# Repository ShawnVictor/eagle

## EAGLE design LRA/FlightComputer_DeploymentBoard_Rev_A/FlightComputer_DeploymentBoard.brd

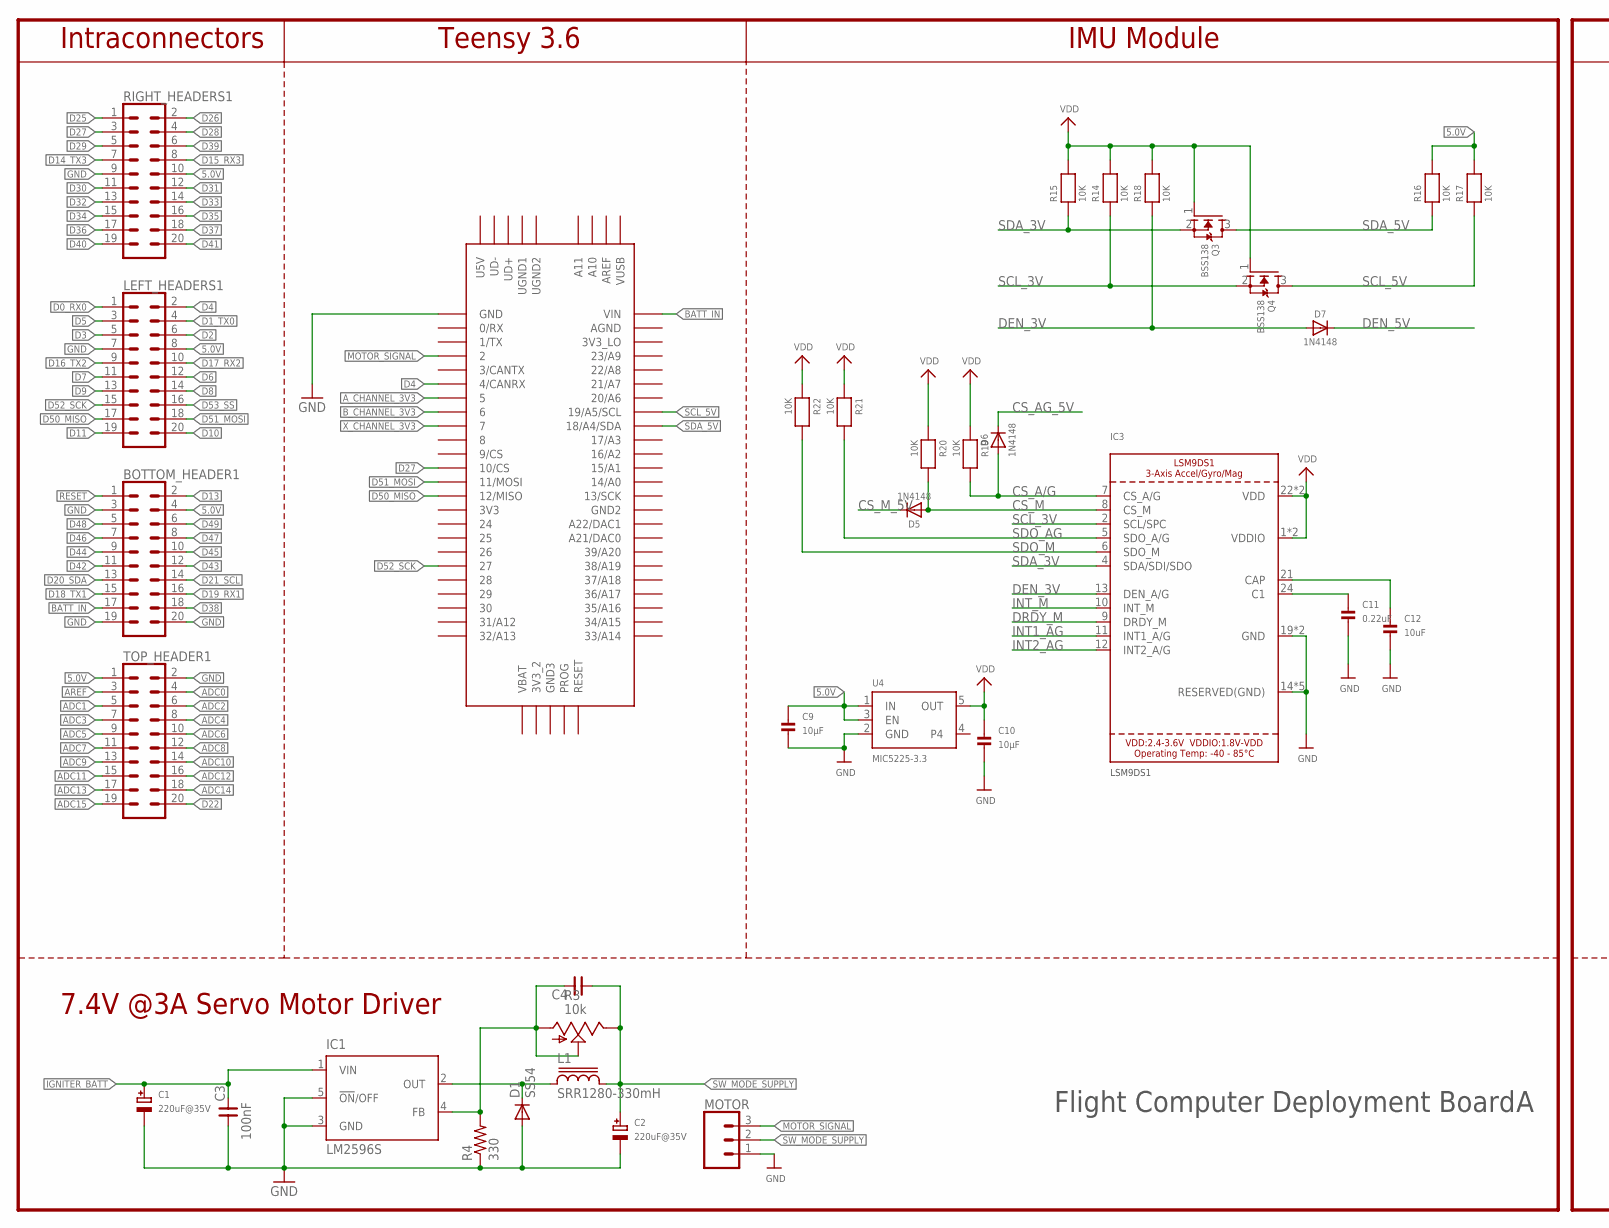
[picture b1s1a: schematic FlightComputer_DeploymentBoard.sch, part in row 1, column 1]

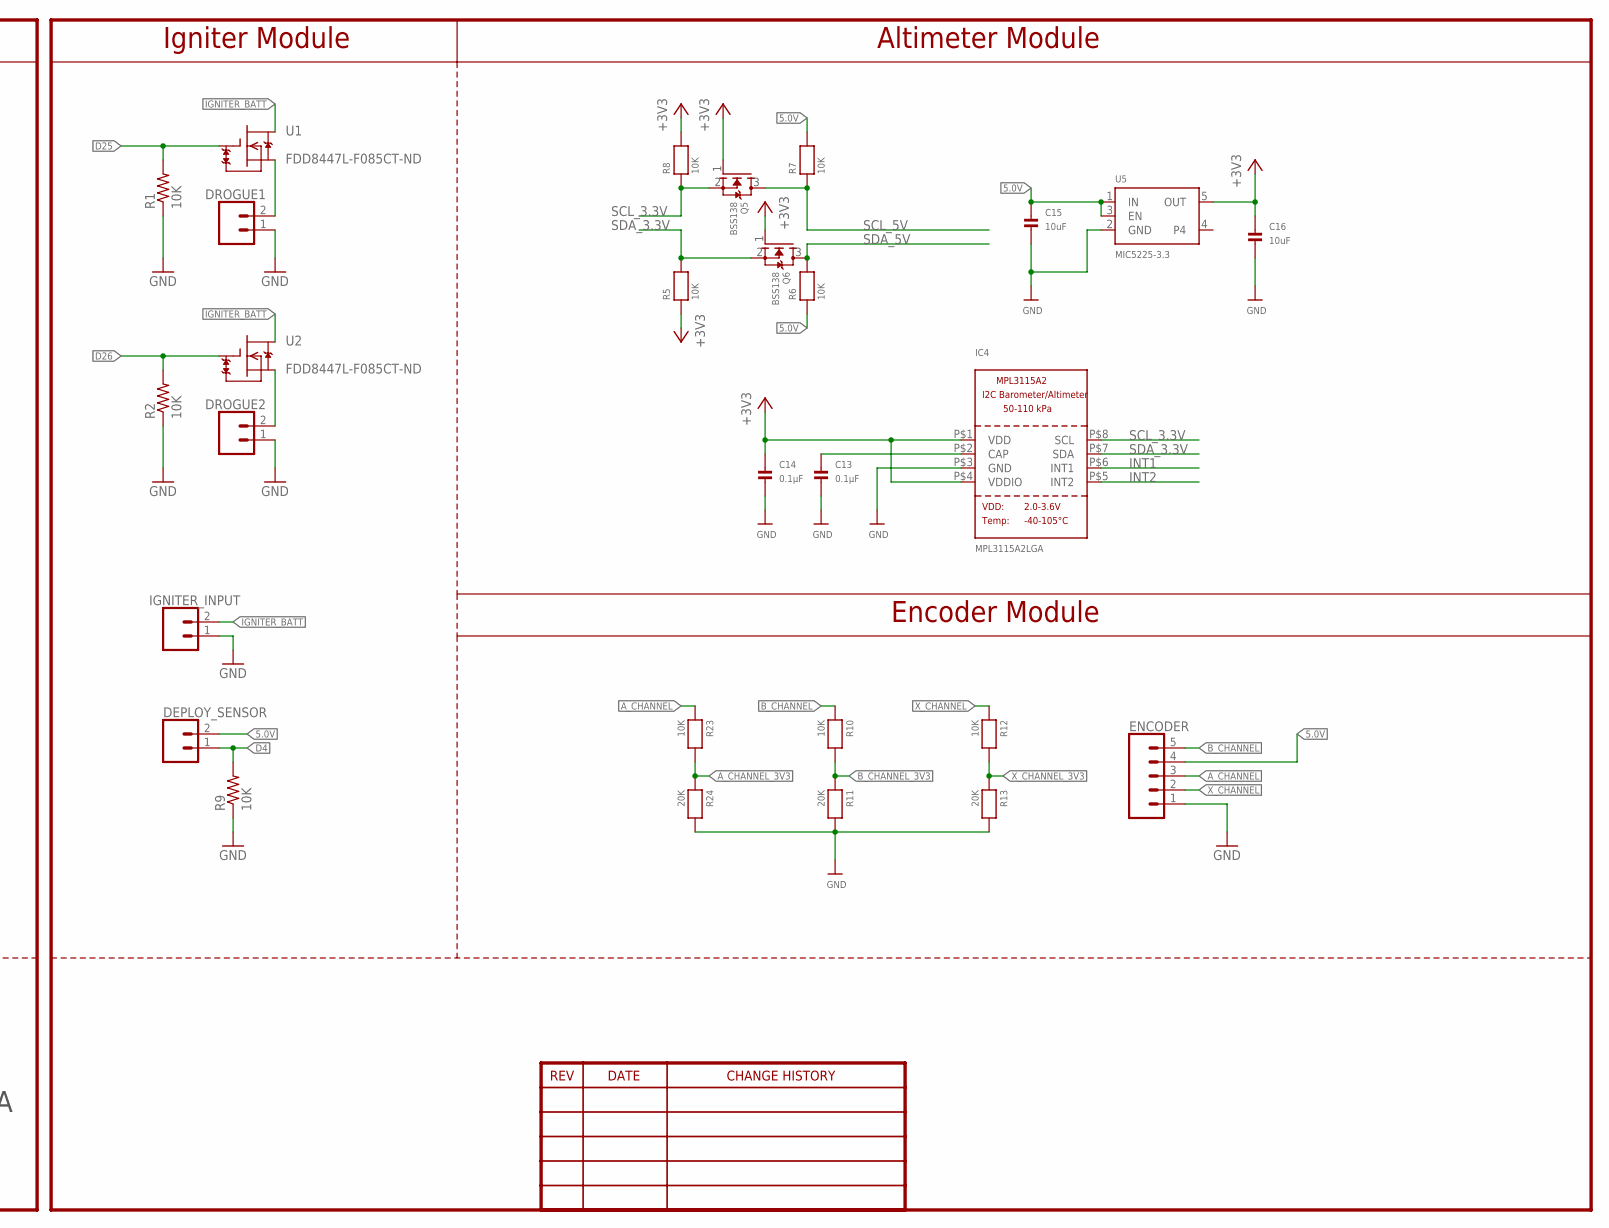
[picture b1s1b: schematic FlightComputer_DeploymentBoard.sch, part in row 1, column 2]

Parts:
BOTTOM_HEADER1: CONN_10X2; 2X10
C1, C2: 220uF@35V; PANASONIC_D
C3: 100nF; 0603
C4: CNP-0603; 0603
C9, C10: 10µF; 0603
C11: 0.22uF; 0603
C12, C15, C16: 10uF; 0603
C13, C14: 0.1µF; 0603
D1: SS54; DO214AB
D5, D6, D7: 1N4148; SOD-323
DEPLOY_SENSOR: CONN_023.5MM; SCREWTERMINAL-3.5MM-2
DROGUE1, DROGUE2: CONN_023.5MM; SCREWTERMINAL-3.5MM-2
ENCODER: CONN_05; 1X05
IC1: LM2596S; TO263-5
IC3: LSM9DS1; LGA24_3.5X3.1MM
IC4: MPL3115A2LGA; LGA8
IGNITER_INPUT: CONN_02; 1X02
L1: SRR1280-330mH; SRR1280
LEFT_HEADERS1: CONN_10X2; 2X10
MOTOR: CONN_03; 1X03
Q3, Q4, Q5, Q6: BSS138; SOT23-WIDE
R1, R2, R9: 10K; R0805
R3: 10k; S64W
R4: 330; R0603
R5, R6, R7, R8, R10, R12, R14, R15, R16, R17, R18, R19, R20, R21, R22, R23: 10K; 0603
R11, R13, R24: 20K; 0603
RIGHT_HEADERS1: CONN_10X2; 2X10
TOP_HEADER1: CONN_10X2; 2X10
U1, U2: FDD8447L-F085CT-ND; TO252
U4, U5: MIC5225-3.3; SOT23-5
U$1: TEENSY_3.5/3.6

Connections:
5.0V: BOTTOM_HEADER1.4, C9.1, C15.1, DEPLOY_SENSOR.2, ENCODER.4, LEFT_HEADERS1.8, R6.1, R7.2, R16.2, R17.2, RIGHT_HEADERS1.10, TOP_HEADER1.1, U4.1 (IN), U4.3 (EN), U5.1 (IN), U5.3 (EN)
+3V3: C14.1, C16.1, IC4.P$1 (VDD), IC4.P$4 (VDDIO), Q5.1 (G), Q6.1 (G), R5.1, R8.2, U5.5 (OUT)
ADC0: TOP_HEADER1.4
ADC1: TOP_HEADER1.5
ADC2: TOP_HEADER1.6
ADC3: TOP_HEADER1.7
ADC4: TOP_HEADER1.8
ADC5: TOP_HEADER1.9
ADC6: TOP_HEADER1.10
ADC7: TOP_HEADER1.11
ADC8: TOP_HEADER1.12
ADC9: TOP_HEADER1.13
ADC10: TOP_HEADER1.14
ADC11: TOP_HEADER1.15
ADC12: TOP_HEADER1.16
ADC13: TOP_HEADER1.17
ADC14: TOP_HEADER1.18
ADC15: TOP_HEADER1.19
AREF: TOP_HEADER1.3
A_CHANNEL: ENCODER.3, R23.1
A_CHANNEL_3V3: R23.2, R24.1, U$1.5
BATT_IN: BOTTOM_HEADER1.17, U$1.VIN
B_CHANNEL: ENCODER.5, R10.1
B_CHANNEL_3V3: R10.2, R11.1, U$1.6
C2: C11.1, IC3.24 (C1)
CAP1: C12.1, IC3.21 (CAP)
CAP2: C13.1, IC4.P$2 (CAP)
CS_A/G: D6.A, IC3.7 (CS_A/G), R19.2
CS_AG_5V: D6.C
CS_M: D5.A, IC3.8 (CS_M), R20.2
CS_M_5V: D5.C
D0_RX0: LEFT_HEADERS1.1
D1_TX0: LEFT_HEADERS1.4
D2: LEFT_HEADERS1.6
D3: LEFT_HEADERS1.5
D4: DEPLOY_SENSOR.1, LEFT_HEADERS1.2, R9.2, U$1.4/CANRX
D5: LEFT_HEADERS1.3
D6: LEFT_HEADERS1.12
D7: LEFT_HEADERS1.11
D8: LEFT_HEADERS1.14
D9: LEFT_HEADERS1.13
D10: LEFT_HEADERS1.20
D11: LEFT_HEADERS1.19
D13: BOTTOM_HEADER1.2
D14_TX3: RIGHT_HEADERS1.7
D15_RX3: RIGHT_HEADERS1.8
D16_TX2: LEFT_HEADERS1.9
D17_RX2: LEFT_HEADERS1.10
D18_TX1: BOTTOM_HEADER1.15
D19_RX1: BOTTOM_HEADER1.16
D20_SDA: BOTTOM_HEADER1.13
D21_SCL: BOTTOM_HEADER1.14
D22: TOP_HEADER1.20
D25: R1.2, RIGHT_HEADERS1.1, U1.G
D26: R2.2, RIGHT_HEADERS1.2, U2.G
D27: RIGHT_HEADERS1.3, U$1.10/CS
D28: RIGHT_HEADERS1.4
D29: RIGHT_HEADERS1.5
D30: RIGHT_HEADERS1.11
D31: RIGHT_HEADERS1.12
D32: RIGHT_HEADERS1.13
D33: RIGHT_HEADERS1.14
D34: RIGHT_HEADERS1.15
D35: RIGHT_HEADERS1.16
D36: RIGHT_HEADERS1.17
D37: RIGHT_HEADERS1.18
D38: BOTTOM_HEADER1.18
D39: RIGHT_HEADERS1.6
D40: RIGHT_HEADERS1.19
D41: RIGHT_HEADERS1.20
D42: BOTTOM_HEADER1.11
D43: BOTTOM_HEADER1.12
D44: BOTTOM_HEADER1.9
D45: BOTTOM_HEADER1.10
D46: BOTTOM_HEADER1.7
D47: BOTTOM_HEADER1.8
D48: BOTTOM_HEADER1.5
D49: BOTTOM_HEADER1.6
D50_MISO: LEFT_HEADERS1.17, U$1.12/MISO
D51_MOSI: LEFT_HEADERS1.18, U$1.11/MOSI
D52_SCK: LEFT_HEADERS1.15, U$1.27
D53_SS: LEFT_HEADERS1.16
DEN_3V: D7.A, IC3.13 (DEN_A/G), R18.1
DEN_5V: D7.C
DRDY_M: IC3.9 (DRDY_M)
GND: BOTTOM_HEADER1.3, BOTTOM_HEADER1.19, BOTTOM_HEADER1.20, C1.-, C2.-, C3.1, C9.2, C10.2, C11.2, C12.2, C13.2, C14.2, C15.2, C16.2, D1.A, DROGUE1.1, DROGUE2.1, ENCODER.1, IC1.3 (GND), IC1.5 (!ON!/OFF), IC3.14 (RESERVED(GND)), IC3.15 (RESERVED(GND)), IC3.16 (RESERVED(GND)), IC3.17 (RESERVED(GND)), IC3.18 (RESERVED(GND)), IC3.19 (GND), IC3.20 (GND), IC4.P$3 (GND), IGNITER_INPUT.1, LEFT_HEADERS1.7, MOTOR.1, R1.1, R2.1, R4.1, R9.1, R11.2, R13.2, R24.2, RIGHT_HEADERS1.9, TOP_HEADER1.2, U4.2 (GND), U5.2 (GND), U$1.GND
IGNITER_BATT: C1.+, C3.2, IC1.1 (VIN), IGNITER_INPUT.2, U1.D, U2.D
INT1: IC4.P$6 (INT1)
INT1_AG: IC3.11 (INT1_A/G)
INT2: IC4.P$5 (INT2)
INT2_AG: IC3.12 (INT2_A/G)
INT_M: IC3.10 (INT_M)
MOTOR_SIGNAL: MOTOR.3, U$1.2
unnamed: D1.C, IC1.2 (OUT), L1.1
unnamed: C4.2, IC1.4 (FB), R3.A, R3.S, R4.2
RESET: BOTTOM_HEADER1.1
SCL_3.3V: IC4.P$8 (SCL), Q5.2 (S), R8.1
SCL_3V: IC3.2 (SCL/SPC), Q4.2 (S), R14.1
SCL_5V: Q4.3 (D), Q5.3 (D), R7.1, R17.1, U$1.19/A5/SCL
SDA_3.3V: IC4.P$7 (SDA), Q6.2 (S), R5.2
SDA_3V: IC3.4 (SDA/SDI/SDO), Q3.2 (S), R15.1
SDA_5V: Q3.3 (D), Q6.3 (D), R6.2, R16.1, U$1.18/A4/SDA
SDO_AG: IC3.5 (SDO_A/G), R21.2
SDO_M: IC3.6 (SDO_M), R22.2
SOURCE: DROGUE1.2, U1.S
SOURCE1: DROGUE2.2, U2.S
SW_MODE_SUPPLY: C2.+, C4.1, L1.2, MOTOR.2, R3.E
VDD: C10.1, IC3.1 (VDDIO), IC3.3 (VDDIO), IC3.22 (VDD), IC3.23 (VDD), Q3.1 (G), Q4.1 (G), R14.2, R15.2, R18.2, R19.1, R20.1, R21.1, R22.1, U4.5 (OUT)
X_CHANNEL: ENCODER.2, R12.1
X_CHANNEL_3V3: R12.2, R13.1, U$1.7

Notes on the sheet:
Intraconnectors
Teensy 3.6
IMU Module
7.4V @3A Servo Motor Driver
Igniter Module
Altimeter Module
Encoder Module
Flight Computer Deployment Board

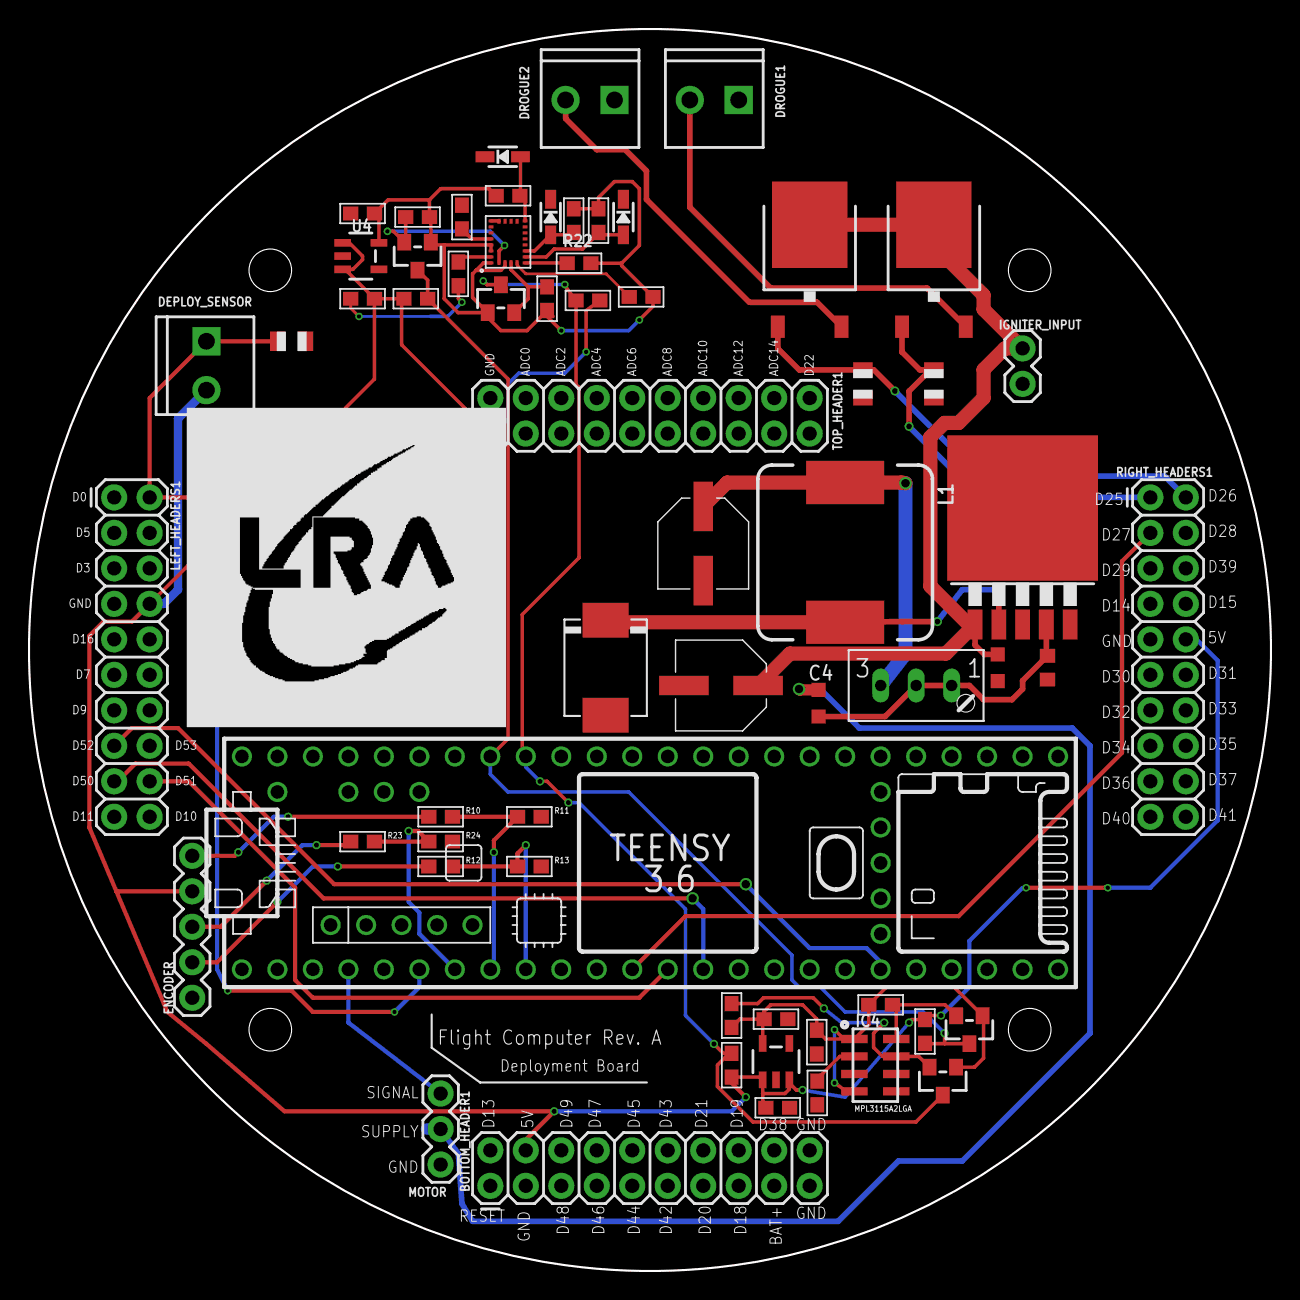
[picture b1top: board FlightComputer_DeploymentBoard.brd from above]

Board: 2 copper layers, 88.9 x 88.9 mm, 63 parts (0 on the bottom side), 39 nets.

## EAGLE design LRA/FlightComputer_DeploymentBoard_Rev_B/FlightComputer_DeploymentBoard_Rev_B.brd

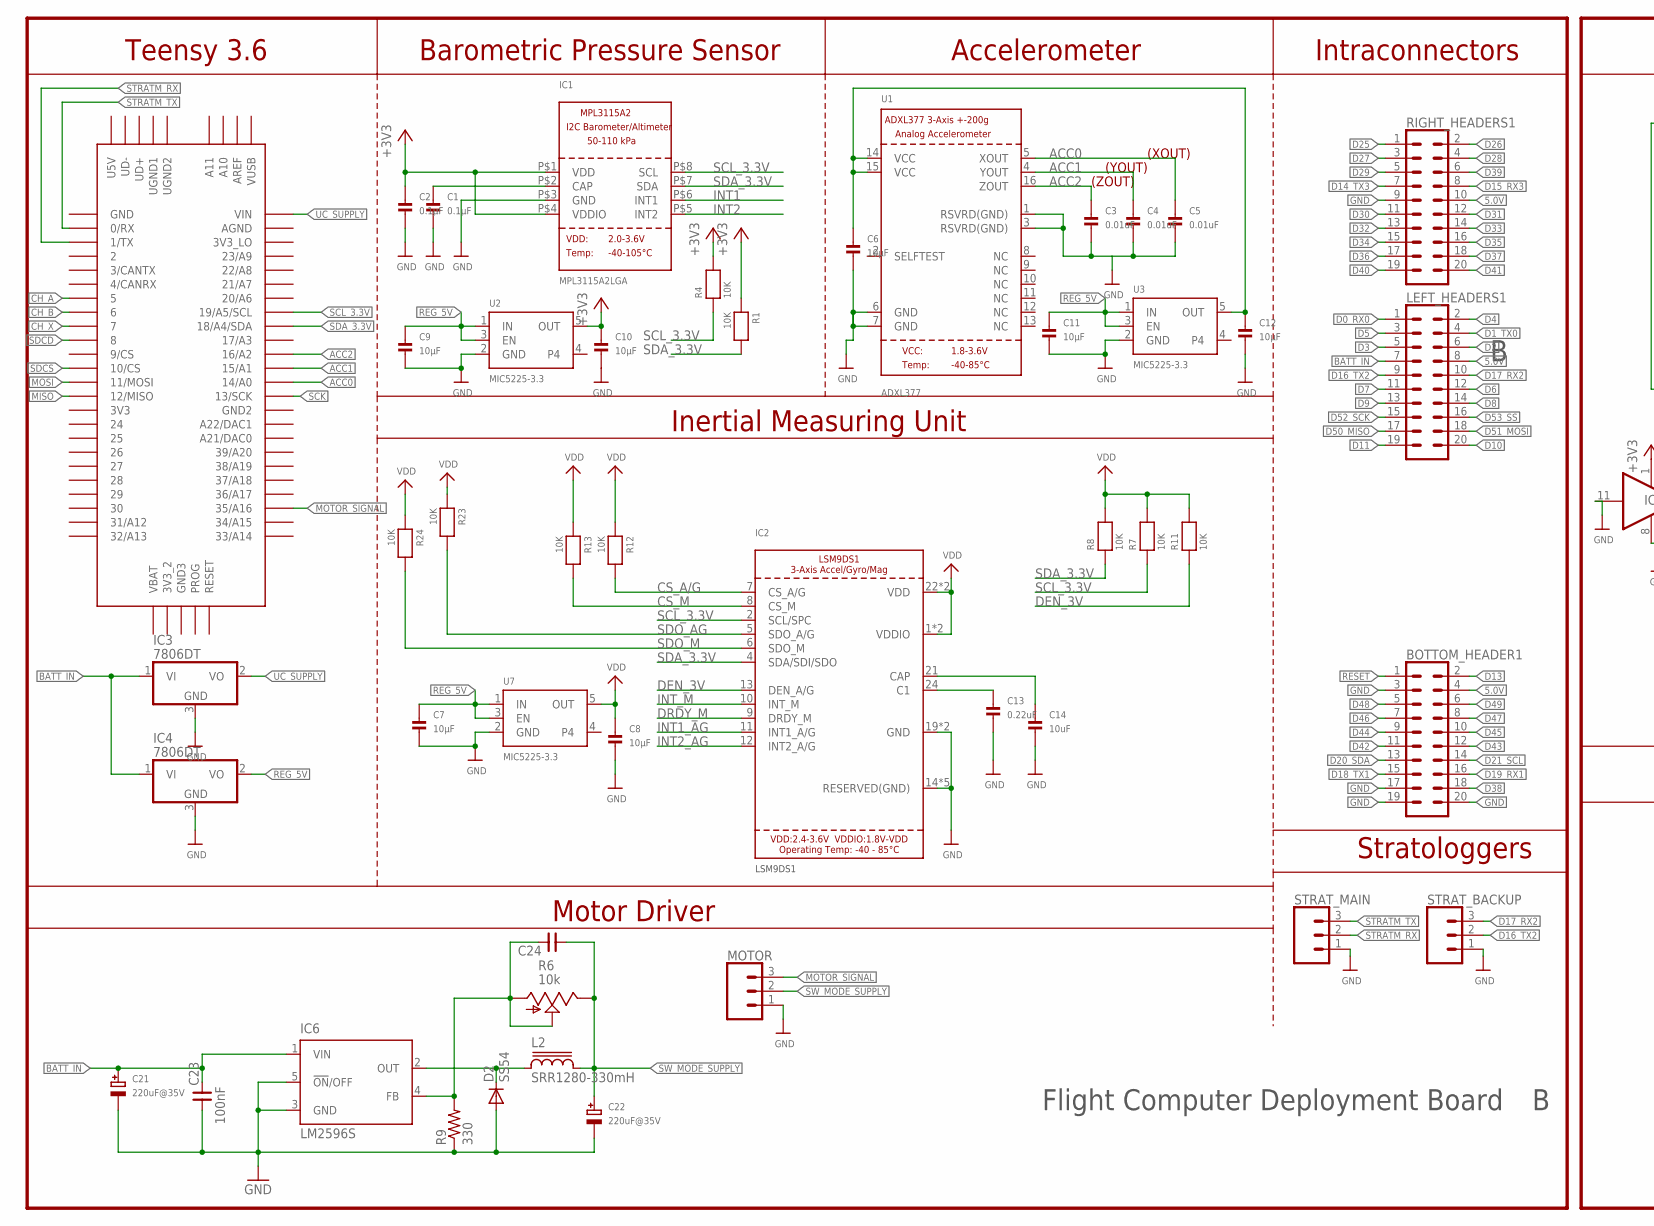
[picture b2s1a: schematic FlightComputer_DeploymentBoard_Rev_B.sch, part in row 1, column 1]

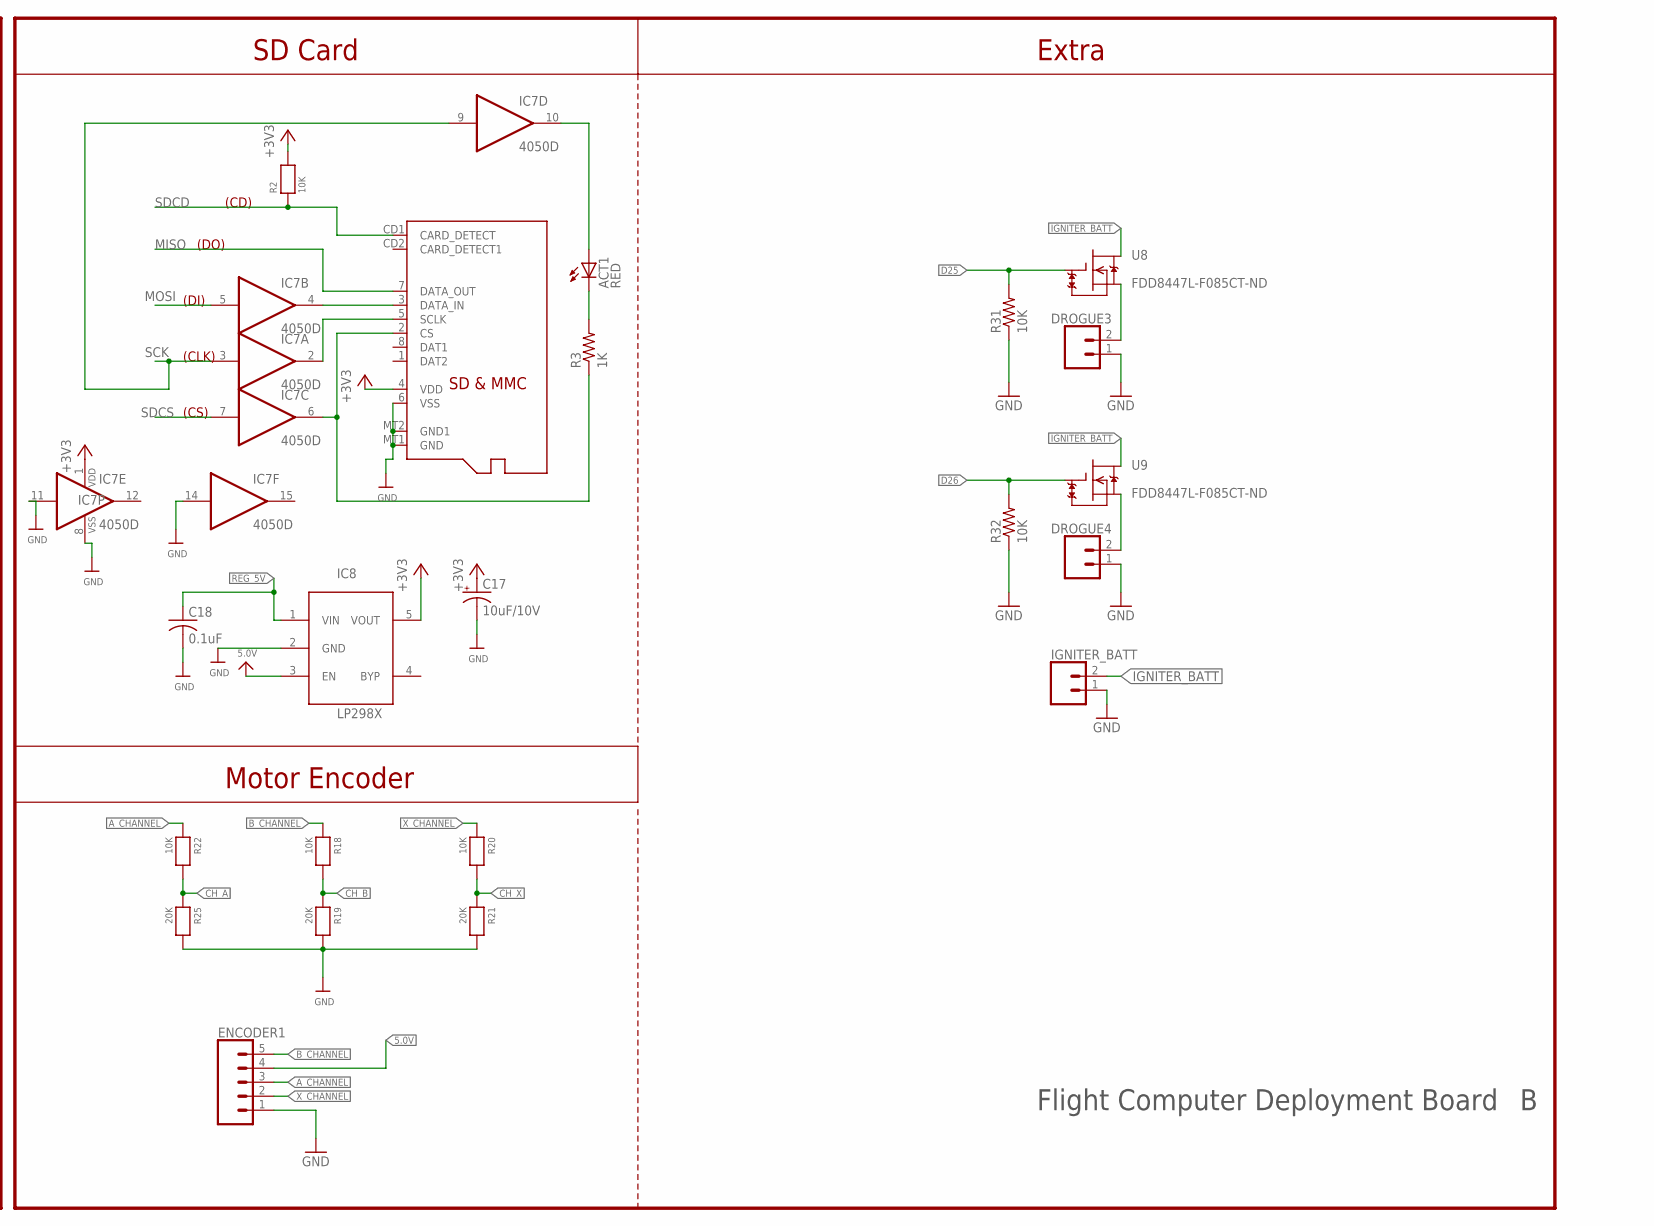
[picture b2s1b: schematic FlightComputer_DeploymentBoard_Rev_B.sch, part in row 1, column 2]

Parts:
ACT1: RED; CHIP-LED0805
BOTTOM_HEADER1: CONN_10X2; 2X10
C1, C2: 0.1µF; 0603
C3, C4, C5: 0.01uF; 0603
C6, C7, C8, C9, C10, C11, C12: 10µF; 0603
C13: 0.22uF; 0603
C14: 10uF; 0603
C17: 10uF/10V; A/3216-18R
C18: 0.1uF; C0805K
C21, C22: 220uF@35V; PANASONIC_D
C23: 100nF; 0603
C24: CNP-0603; 0603
D2: SS54; DO214AB
DROGUE3, DROGUE4: CONN_023.5MM; SCREWTERMINAL-3.5MM-2
ENCODER1: CONN_05; 1X05
IC1: MPL3115A2LGA; LGA8
IC2: LSM9DS1; LGA24_3.5X3.1MM
IC3, IC4: 7806DT; TO252
IC6: LM2596S; TO263-5
IC7: 4050D; SO16
IC8: LP298XS; SOT23-5L
IGNITER_BATT: CONN_02; 1X02
L2: SRR1280-330mH; SRR1280
LEFT_HEADERS1: CONN_10X2; 2X10
MOTOR: CONN_03; 1X03
R1, R2, R4, R7, R8, R11, R12, R13, R18, R20, R22, R23, R24: 10K; 0603
R3: 1K; R0805
R6: 10k; S64W
R9: 330; R0603
R19, R21, R25: 20K; 0603
R31, R32: 10K; R0805
RIGHT_HEADERS1: CONN_10X2; 2X10
STRAT_BACKUP: CONN_03; 1X03
STRAT_MAIN: CONN_03; 1X03
U1: ADXL377; LFCSP16_LQ
U2, U3, U7: MIC5225-3.3; SOT23-5
U8, U9: FDD8447L-F085CT-ND; TO252
U$1: TEENSY_3.5/3.6
U$38: STRATOLOGGER
X2: MICROSD

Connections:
5.0V: BOTTOM_HEADER1.4, ENCODER1.4, IC8.3 (EN), LEFT_HEADERS1.8, RIGHT_HEADERS1.10
+3V3: C2.1, C10.1, C17.+, IC1.P$1 (VDD), IC1.P$4 (VDDIO), IC7.1 (VDD), IC8.5 (VOUT), R1.1, R2.2, R4.2, U2.5 (OUT), X2.4 (VDD)
ACC0: C5.1, U1.5 (XOUT), U$1.14/A0
ACC1: C4.1, U1.4 (YOUT), U$1.15/A1
ACC2: C3.1, U1.16 (ZOUT), U$1.16/A2
A_CHANNEL: ENCODER1.3, R22.1
BATT_IN: C21.+, C23.2, IC3.1 (VI), IC4.1 (VI), IC6.1 (VIN), LEFT_HEADERS1.7
B_CHANNEL: ENCODER1.5, R18.1
C1: C13.1, IC2.24 (C1)
CAP1: C1.1, IC1.P$2 (CAP)
CAP3: C14.1, IC2.21 (CAP)
CH_A: R22.2, R25.1, U$1.5
CH_B: R18.2, R19.1, U$1.6
CH_X: R20.2, R21.1, U$1.7
CS_A/G: IC2.7 (CS_A/G), R12.2
CS_M: IC2.8 (CS_M), R13.2
D0_RX0: LEFT_HEADERS1.1
D1_TX0: LEFT_HEADERS1.4
D2: LEFT_HEADERS1.6
D3: LEFT_HEADERS1.5
D4: LEFT_HEADERS1.2
D5: LEFT_HEADERS1.3
D6: LEFT_HEADERS1.12
D7: LEFT_HEADERS1.11
D8: LEFT_HEADERS1.14
D9: LEFT_HEADERS1.13
D10: LEFT_HEADERS1.20
D11: LEFT_HEADERS1.19
D13: BOTTOM_HEADER1.2
D14_TX3: RIGHT_HEADERS1.7
D15_RX3: RIGHT_HEADERS1.8
D16_TX2: LEFT_HEADERS1.9, STRAT_BACKUP.2
D17_RX2: LEFT_HEADERS1.10, STRAT_BACKUP.3
D18_TX1: BOTTOM_HEADER1.15
D19_RX1: BOTTOM_HEADER1.16
D20_SDA: BOTTOM_HEADER1.13
D21_SCL: BOTTOM_HEADER1.14
D25: R31.2, RIGHT_HEADERS1.1, U8.G
D26: R32.2, RIGHT_HEADERS1.2, U9.G
D27: RIGHT_HEADERS1.3
D28: RIGHT_HEADERS1.4
D29: RIGHT_HEADERS1.5
D30: RIGHT_HEADERS1.11
D31: RIGHT_HEADERS1.12
D32: RIGHT_HEADERS1.13
D33: RIGHT_HEADERS1.14
D34: RIGHT_HEADERS1.15
D35: RIGHT_HEADERS1.16
D36: RIGHT_HEADERS1.17
D37: RIGHT_HEADERS1.18
D38: BOTTOM_HEADER1.18
D39: RIGHT_HEADERS1.6
D40: RIGHT_HEADERS1.19
D41: RIGHT_HEADERS1.20
D42: BOTTOM_HEADER1.11
D43: BOTTOM_HEADER1.12
D44: BOTTOM_HEADER1.9
D45: BOTTOM_HEADER1.10
D46: BOTTOM_HEADER1.7
D47: BOTTOM_HEADER1.8
D48: BOTTOM_HEADER1.5
D49: BOTTOM_HEADER1.6
D50_MISO: LEFT_HEADERS1.17
D51_MOSI: LEFT_HEADERS1.18
D52_SCK: LEFT_HEADERS1.15
D53_SS: LEFT_HEADERS1.16
DEN_3V: IC2.13 (DEN_A/G), R11.1
DRDY_M: IC2.9 (DRDY_M)
GND: BOTTOM_HEADER1.3, BOTTOM_HEADER1.17, BOTTOM_HEADER1.19, BOTTOM_HEADER1.20, C1.2, C2.2, C3.2, C4.2, C5.2, C6.2, C7.2, C8.2, C9.2, C10.2, C11.2, C12.2, C13.2, C14.2, C17.-, C18.2, C21.-, C22.-, C23.1, D2.A, DROGUE3.1, DROGUE4.1, ENCODER1.1, IC1.P$3 (GND), IC2.14 (RESERVED(GND)), IC2.15 (RESERVED(GND)), IC2.16 (RESERVED(GND)), IC2.17 (RESERVED(GND)), IC2.18 (RESERVED(GND)), IC2.19 (GND), IC2.20 (GND), IC3.3 (GND), IC4.3 (GND), IC6.3 (GND), IC6.5 (!ON!/OFF), IC7.8 (VSS), IC7.11 (I), IC7.14 (I), IC8.2 (GND), IGNITER_BATT.1, MOTOR.1, R9.1, R19.2, R21.2, R25.2, R31.1, R32.1, RIGHT_HEADERS1.9, STRAT_BACKUP.1, STRAT_MAIN.1, U1.1 (RSVRD(GND)), U1.3 (RSVRD(GND)), U1.6 (GND), U1.7 (GND), U2.2 (GND), U3.2 (GND), U7.2 (GND), X2.6 (VSS), X2.MT1 (GND), X2.MT2 (GND1)
IGNITER_BATT: IGNITER_BATT.2, U8.D, U9.D
INT1: IC1.P$6 (INT1)
INT1_AG: IC2.11 (INT1_A/G)
INT2: IC1.P$5 (INT2)
INT2_AG: IC2.12 (INT2_A/G)
INT_M: IC2.10 (INT_M)
MISO: U$1.12/MISO, X2.7 (DATA_OUT)
MOSI: IC7.5 (I), U$1.11/MOSI
MOTOR_SIGNAL: MOTOR.3, U$1.35/A16
unnamed: ACT1.A, IC7.10 (O)
unnamed: IC7.2 (O), X2.5 (SCLK)
unnamed: IC7.6 (O), R3.1, X2.2 (CS)
unnamed: ACT1.C, R3.2
unnamed: IC7.4 (O), X2.3 (DATA_IN)
unnamed: D2.C, IC6.2 (OUT), L2.1
unnamed: C24.2, IC6.4 (FB), R6.A, R6.S, R9.2
unnamed: C6.1, C12.1, U1.14 (VCC), U1.15 (VCC), U3.5 (OUT)
REG_5V: C7.1, C9.1, C11.1, C18.1, IC4.2 (VO), IC8.1 (VIN), U2.1 (IN), U2.3 (EN), U3.1 (IN), U3.3 (EN), U7.1 (IN), U7.3 (EN)
RESET: BOTTOM_HEADER1.1
SCK: IC7.3 (I), IC7.9 (I), U$1.13/SCK
SCL_3.3V: IC1.P$8 (SCL), IC2.2 (SCL/SPC), R4.1, R7.1, U$1.19/A5/SCL
SDA_3.3V: IC1.P$7 (SDA), IC2.4 (SDA/SDI/SDO), R1.2, R8.1, U$1.18/A4/SDA
SDCD: R2.1, U$1.8, X2.CD1 (CARD_DETECT)
SDCS: IC7.7 (I), U$1.10/CS
SDO_AG: IC2.5 (SDO_A/G), R23.2
SDO_M: IC2.6 (SDO_M), R24.2
SOURCE2: DROGUE3.2, U8.S
SOURCE3: DROGUE4.2, U9.S
STRATM_RX: STRAT_MAIN.2, U$1.1/TX
STRATM_TX: STRAT_MAIN.3, U$1.0/RX
SW_MODE_SUPPLY: C22.+, C24.1, L2.2, MOTOR.2, R6.E
UC_SUPPLY: IC3.2 (VO), U$1.VIN
VDD: C8.1, IC2.1 (VDDIO), IC2.3 (VDDIO), IC2.22 (VDD), IC2.23 (VDD), R7.2, R8.2, R11.2, R12.1, R13.1, R23.1, R24.1, U7.5 (OUT)
X_CHANNEL: ENCODER1.2, R20.1

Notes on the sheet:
Teensy 3.6
Intraconnectors
Barometric Pressure Sensor
(XOUT)
(YOUT)
(ZOUT)
Accelerometer
Inertial Measuring Unit
(CD)
(DO)
(DI)
(CLK)
(CS)
SD Card
Motor Driver
Stratologgers
Flight Computer Deployment Board
Motor Encoder
Extra

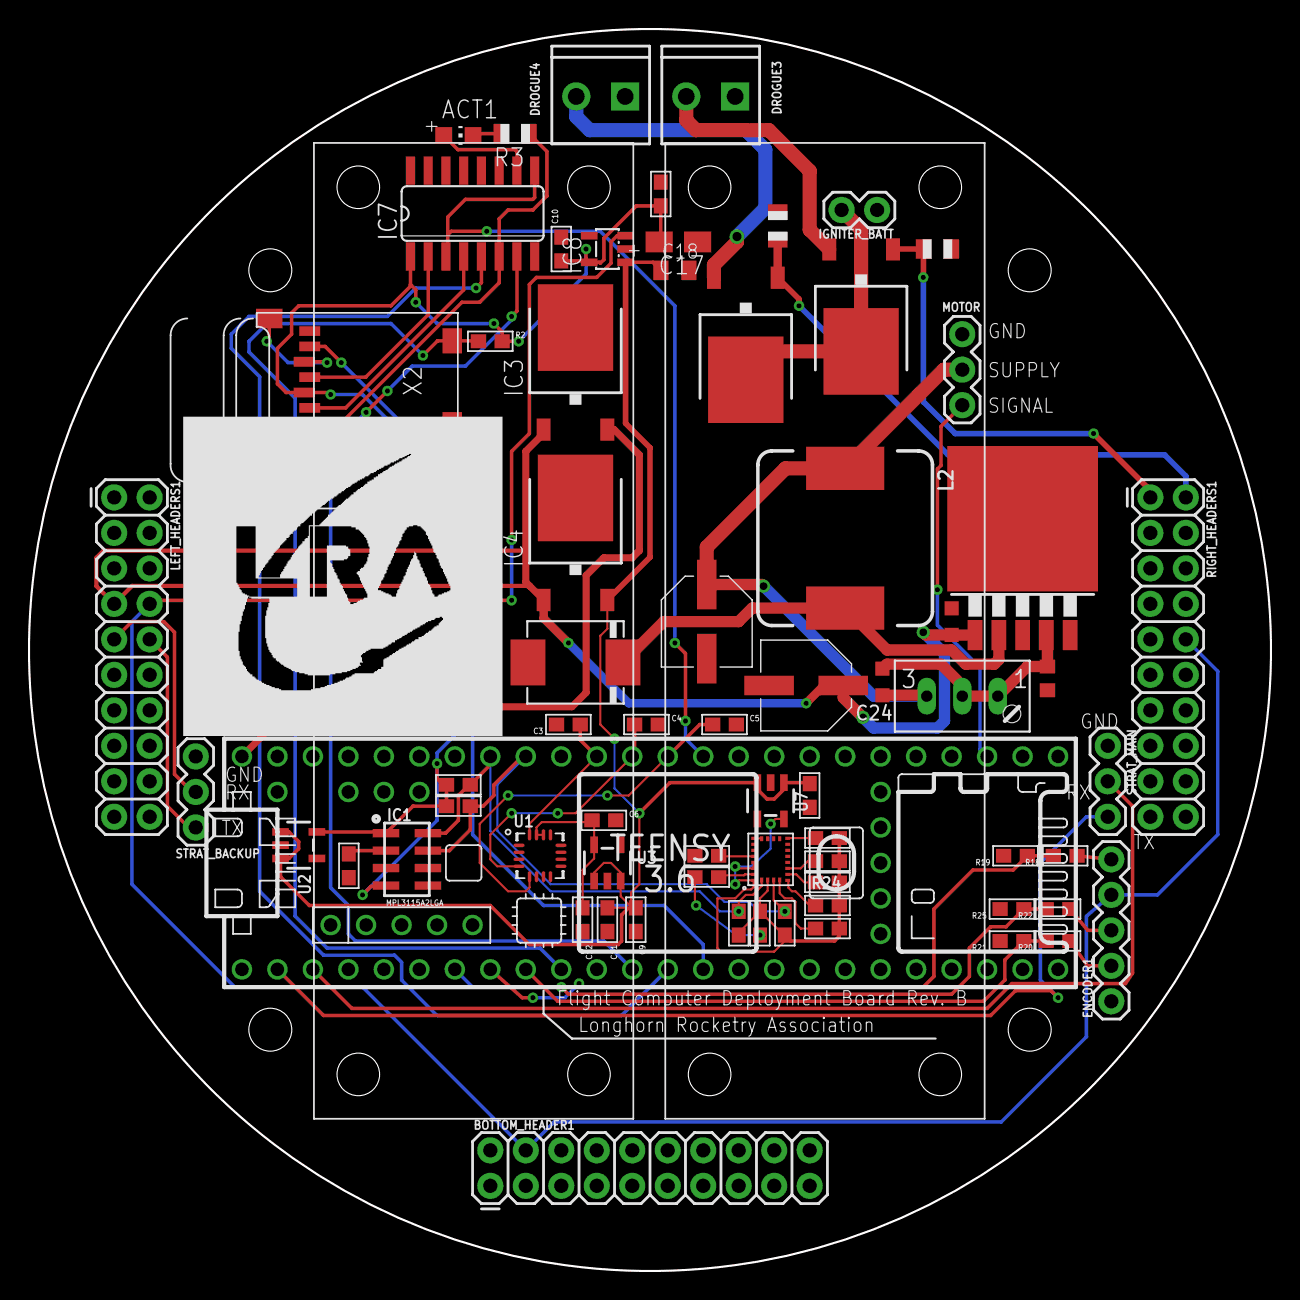
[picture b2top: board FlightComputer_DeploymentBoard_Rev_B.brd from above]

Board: 2 copper layers, 88.9 x 88.9 mm, 71 parts (0 on the bottom side), 50 nets.

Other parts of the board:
U$36: STRATOLOGGER

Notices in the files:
parts and their libraries:
SparkFun-Connectors: Licensing: Creative Commons ShareAlike 4.0 International - https://creativecommons.org/licenses/by-sa/4.0
inductor-bourns: Copyright (C) 2008, Bob Starr
dframes: Copyright (C) 2004, Bob Starr (bobstarr@mindspring.com)
